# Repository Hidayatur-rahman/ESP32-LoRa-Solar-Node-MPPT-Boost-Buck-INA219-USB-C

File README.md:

# ESP32 LoRa Solar Node Meshtastic Board

A solar-powered ESP32 + LoRa (RFM95W) node board. It charges a single-cell Li-ion battery from a solar panel with MPPT (CN3791), generates stable 5V and 3.3V rails, monitors battery voltage and current (INA219), and programs over USB-C (CH340C with auto-reset).

**Board:** 2-layer PCB, 75 × 70 mm, 1.6 mm  
**Design tool:** KiCad 10  
**Revision:**  rev 1, 2026-10-13

## Table of Contents

- [3D View](#3d-view)
- [PCB](#pcb)
- [Features](#features)
- [Power Path](#power-path)
- [Pin Mapping](#pin-mapping)
- [Connectors](#connectors)
- [Solder Jumpers](#solder-jumpers)
- [MPPT Voltage Setting (CN3791)](#mppt-voltage-setting-cn3791)
- [MPPT Test Result](#mppt-test-result-bench-power-supply)
- [Main Components](#main-components)
- [Usage Notes](#usage-notes)
- [Firmware](#firmware)
- [Roadmap](#roadmap)
- [License](#license)
- [Disclaimer](#disclaimer)

## 3d View

## PCB

## Features

- ESP32-WROOM-32 module
- LoRa radio: RFM95W-915S2 (915 MHz) with U.FL antenna connector
- Solar MPPT charger: CN3791 for a 1S Li-ion/LiPo battery (4.2 V)
- Solder jumpers to set the solar panel MPPT voltage: 5 V / 9 V / 12 V / 18 V
- P-MOSFET (AOD4185) in the solar charge path
- INA219 current/voltage monitor with a 10 mΩ shunt on the battery line
- MT3608 boost converter (battery → 5 V)
- STI3408B buck converter (5 V → 3.3 V)
- USB-C programming port with CH340C and automatic reset/boot (DTR/RTS)
- Charge and done LEDs from the CN3791
- 2 × I2C ports and 3 × ADC sensor ports (JST-EH), each with selectable sensor supply (5 V or 3.3 V)
- Reset and Boot buttons
- Test points for 3.3 V, 5 V and 4.2 V
- 0 Ω links in the power path (useful for measuring current or isolating a section)

## Power Path

```
Solar panel ──► Q1 (P-MOSFET) ──► CN3791 MPPT ──► INA219 shunt ──► Battery (4.2 V)
                                                                       │
ESP32/LoRa / sensors ◄── 3.3 V(STI3408B buck) ◄── 5 V (MT3608 boost) ◄─┘
                                                              
```

> ⚠️ **BATTERY WARNING**  
> This board has **no BMS** and **no reverse polarity protection** on the battery input. The CN3791 only charges the cell, it does not protect it from over-discharge, over-current or short circuit. Connecting the battery the wrong way round can destroy the board and may cause a fire. **Always use a battery that already has a built-in BMS / protection circuit.**

## Pin Mapping

| ESP32 Pin | Function |
|---|---|
| GPIO18 | LoRa SCK |
| GPIO19 | LoRa MISO |
| GPIO23 | LoRa MOSI |
| GPIO4 | LoRa NSS (CS) |
| GPIO14 | LoRa RESET |
| GPIO26 | LoRa DIO0 |
| GPIO27 | LoRa DIO1 |
| GPIO21 | I2C SDA (INA219, J2, J3) |
| GPIO22 | I2C SCL (INA219, J2, J3) |
| GPIO32 | ADC port 1 (J7) |
| GPIO33 | ADC port 2 (J8) |
| GPIO34 | ADC port 3 (J9) |
| GPIO0 | Boot button / auto-reset |
| EN | Reset button / auto-reset |
| GPIO1 / GPIO3 | TX / RX to CH340C |

Each ADC input has a 10 kΩ / 15 kΩ divider, so a 5 V sensor output is scaled to about 3 V.

## Connectors

| Ref | Name | Description |
|---|---|---|
| J1 | USB-C | Programming and serial |
| J4 | U.FL | LoRa antenna |
| J5 | Battery | 1S Li-ion/LiPo (GND, BATT+) |
| J6 | Solar panel | Panel input (VCC, GND) |
| J2, J3 | I2C | SCL, SDA, 3.3 V, GND |
| J7, J8, J9 | ADC | Signal, sensor supply, GND |

## Solder Jumpers

| Ref | Function |
|---|---|
| 5V0, 9V1, 12V2, 18V3 | Select the solar panel MPPT voltage. Close only one. |
| JP1, JP3, JP4 | Select the supply of ADC port 1, 2 and 3: 5 V or 3.3 V |

he CN3791 regulates the solar panel voltage so that the MPPT pin sits at about 1.04 V (typical value from the datasheet; please verify against your datasheet revision). A resistor divider sets the panel voltage:
 
```
VCC (panel) ── R18 200k ──┬── MPPT pin
                          │
                        R_bottom (selected by jumper)
                          │
                         GND
 
V_panel = 1.04 V × (1 + R18 / R_bottom)
```
 
| Jumper | R_bottom | Regulated panel voltage | Suggested panel |
|---|---|---|---|
| 5V0 | R27 = 51 kΩ | ≈ 5.1 V | 5–6 V panel |
| 9V1 | R13 = 27 kΩ | ≈ 8.7 V | 9 V panel |
| 12V2 | R14 = 18 kΩ | ≈ 12.6 V | 12 V panel |
| 18V3 | R15 = 12 kΩ | ≈ 18.4 V | 20 V panel |
 
Use 1 % 0805 resistors. The values above are common values chosen to land close to the target panel voltage (within about 5 %), which is accurate enough because the maximum power point of a panel is fairly flat.
 
To use a different panel, choose the bottom resistor from the panel's maximum power voltage (Vmp):
 
```
R_bottom = R18 / (Vmp / 1.04 − 1)
```
 
Example: Vmp = 17 V → R_bottom = 200k / (17 / 1.04 − 1) ≈ 13 kΩ (use 13 kΩ or the nearest standard value, 12 kΩ or 15 kΩ).
 
Keep the panel's open-circuit voltage (Voc) below the CN3791 input limit (about 28 V).

## Mppt Test Result (Bench Power Supply)

The CN3791 charger was tested with a bench power supply instead of a solar panel, and the INA219 readings were compared with the supply readings.

| Item | Value |
|---|---|
| Input voltage (bench supply) | 18.6 V |
| Input current | 0.49 A |
| Input power | ≈ 9.1 W |
| INA219 bus voltage (battery) | 3.89 V |
| INA219 charge current | 2.04 A |
| Battery charge power | ≈ 7.9 W |
| Estimated efficiency | ≈ 87 % |

## Main Components

| Ref | Part |
|---|---|
| U1 | ESP32-WROOM-32 |
| U2 | RFM95W-915S2 (LoRa) |
| U3 | MT3608 (boost) |
| STI3408B1 | STI3408B (buck) |
| U4 | INA219 |
| U5 | CN3791 (MPPT charger) |
| U6 | CH340C (USB-UART) |
| Q1 | AOD4185 (P-MOSFET) |
| Q4, Q5 | BC847 (auto-reset) |
| RSHUNT1 | 0.01 Ω, 2512 |
| L1, L3 / L2 | 4.7 µH / 22 µH |

## Usage Notes

- Close **only one** MPPT jumper (5V0, 9V1, 12V2 or 18V3), based on your solar panel's maximum power voltage.
- Use a single-cell Li-ion/LiPo battery. The CN3791 in this design charges to 4.2 V.
- The RFM95W-915S2 covers the 915 MHz band. Check the allowed LoRa frequency in your country before use, and always attach an antenna before transmitting.
- Upload firmware over USB-C. Auto-reset is handled by the CH340C, so no button presses are needed.
- INA219 is on the I2C bus together with J2 and J3, so avoid address conflicts with your sensors.
- The INA219 address (0x40) is the default. Check the A0/A1 pins in the schematic if you changed it.

## Firmware

- Firmware: Meshtastic custom build
- Target: `esp32_rfm95_custom`
- Version: `2.8.3`
- Revision: `d9c9916`

| Signal | ESP32 Pin |
|---|---|
| SCK / MISO / MOSI | GPIO18 / GPIO19 / GPIO23 |
| NSS (CS) | GPIO4 |
| RESET | GPIO14 |
| DIO0 / DIO1 | GPIO26 / GPIO27 |
| I2C SDA / SCL | GPIO21 / GPIO22 |

Set the LoRa region in Meshtastic to match your country and the 915 MHz hardware.

## Roadmap
 
**Version 2 (in progress)**
<p align="center">
  
  \
</p>

- 4-layer PCB
- GPS module added

This repository currently contains version 1 (2-layer, no GPS). Version 2 files will be added when the design is ready.

## License

(KiCad schematic, PCB layout and design files): [CERN-OHL-W v2](https://ohwr.org/cern_ohl_w_v2.txt)

## Disclaimer

This is a hobbyist/DIY project. Double-check battery polarity and solar jumper settings before powering on. No warranty is provided — build and use at your own risk.

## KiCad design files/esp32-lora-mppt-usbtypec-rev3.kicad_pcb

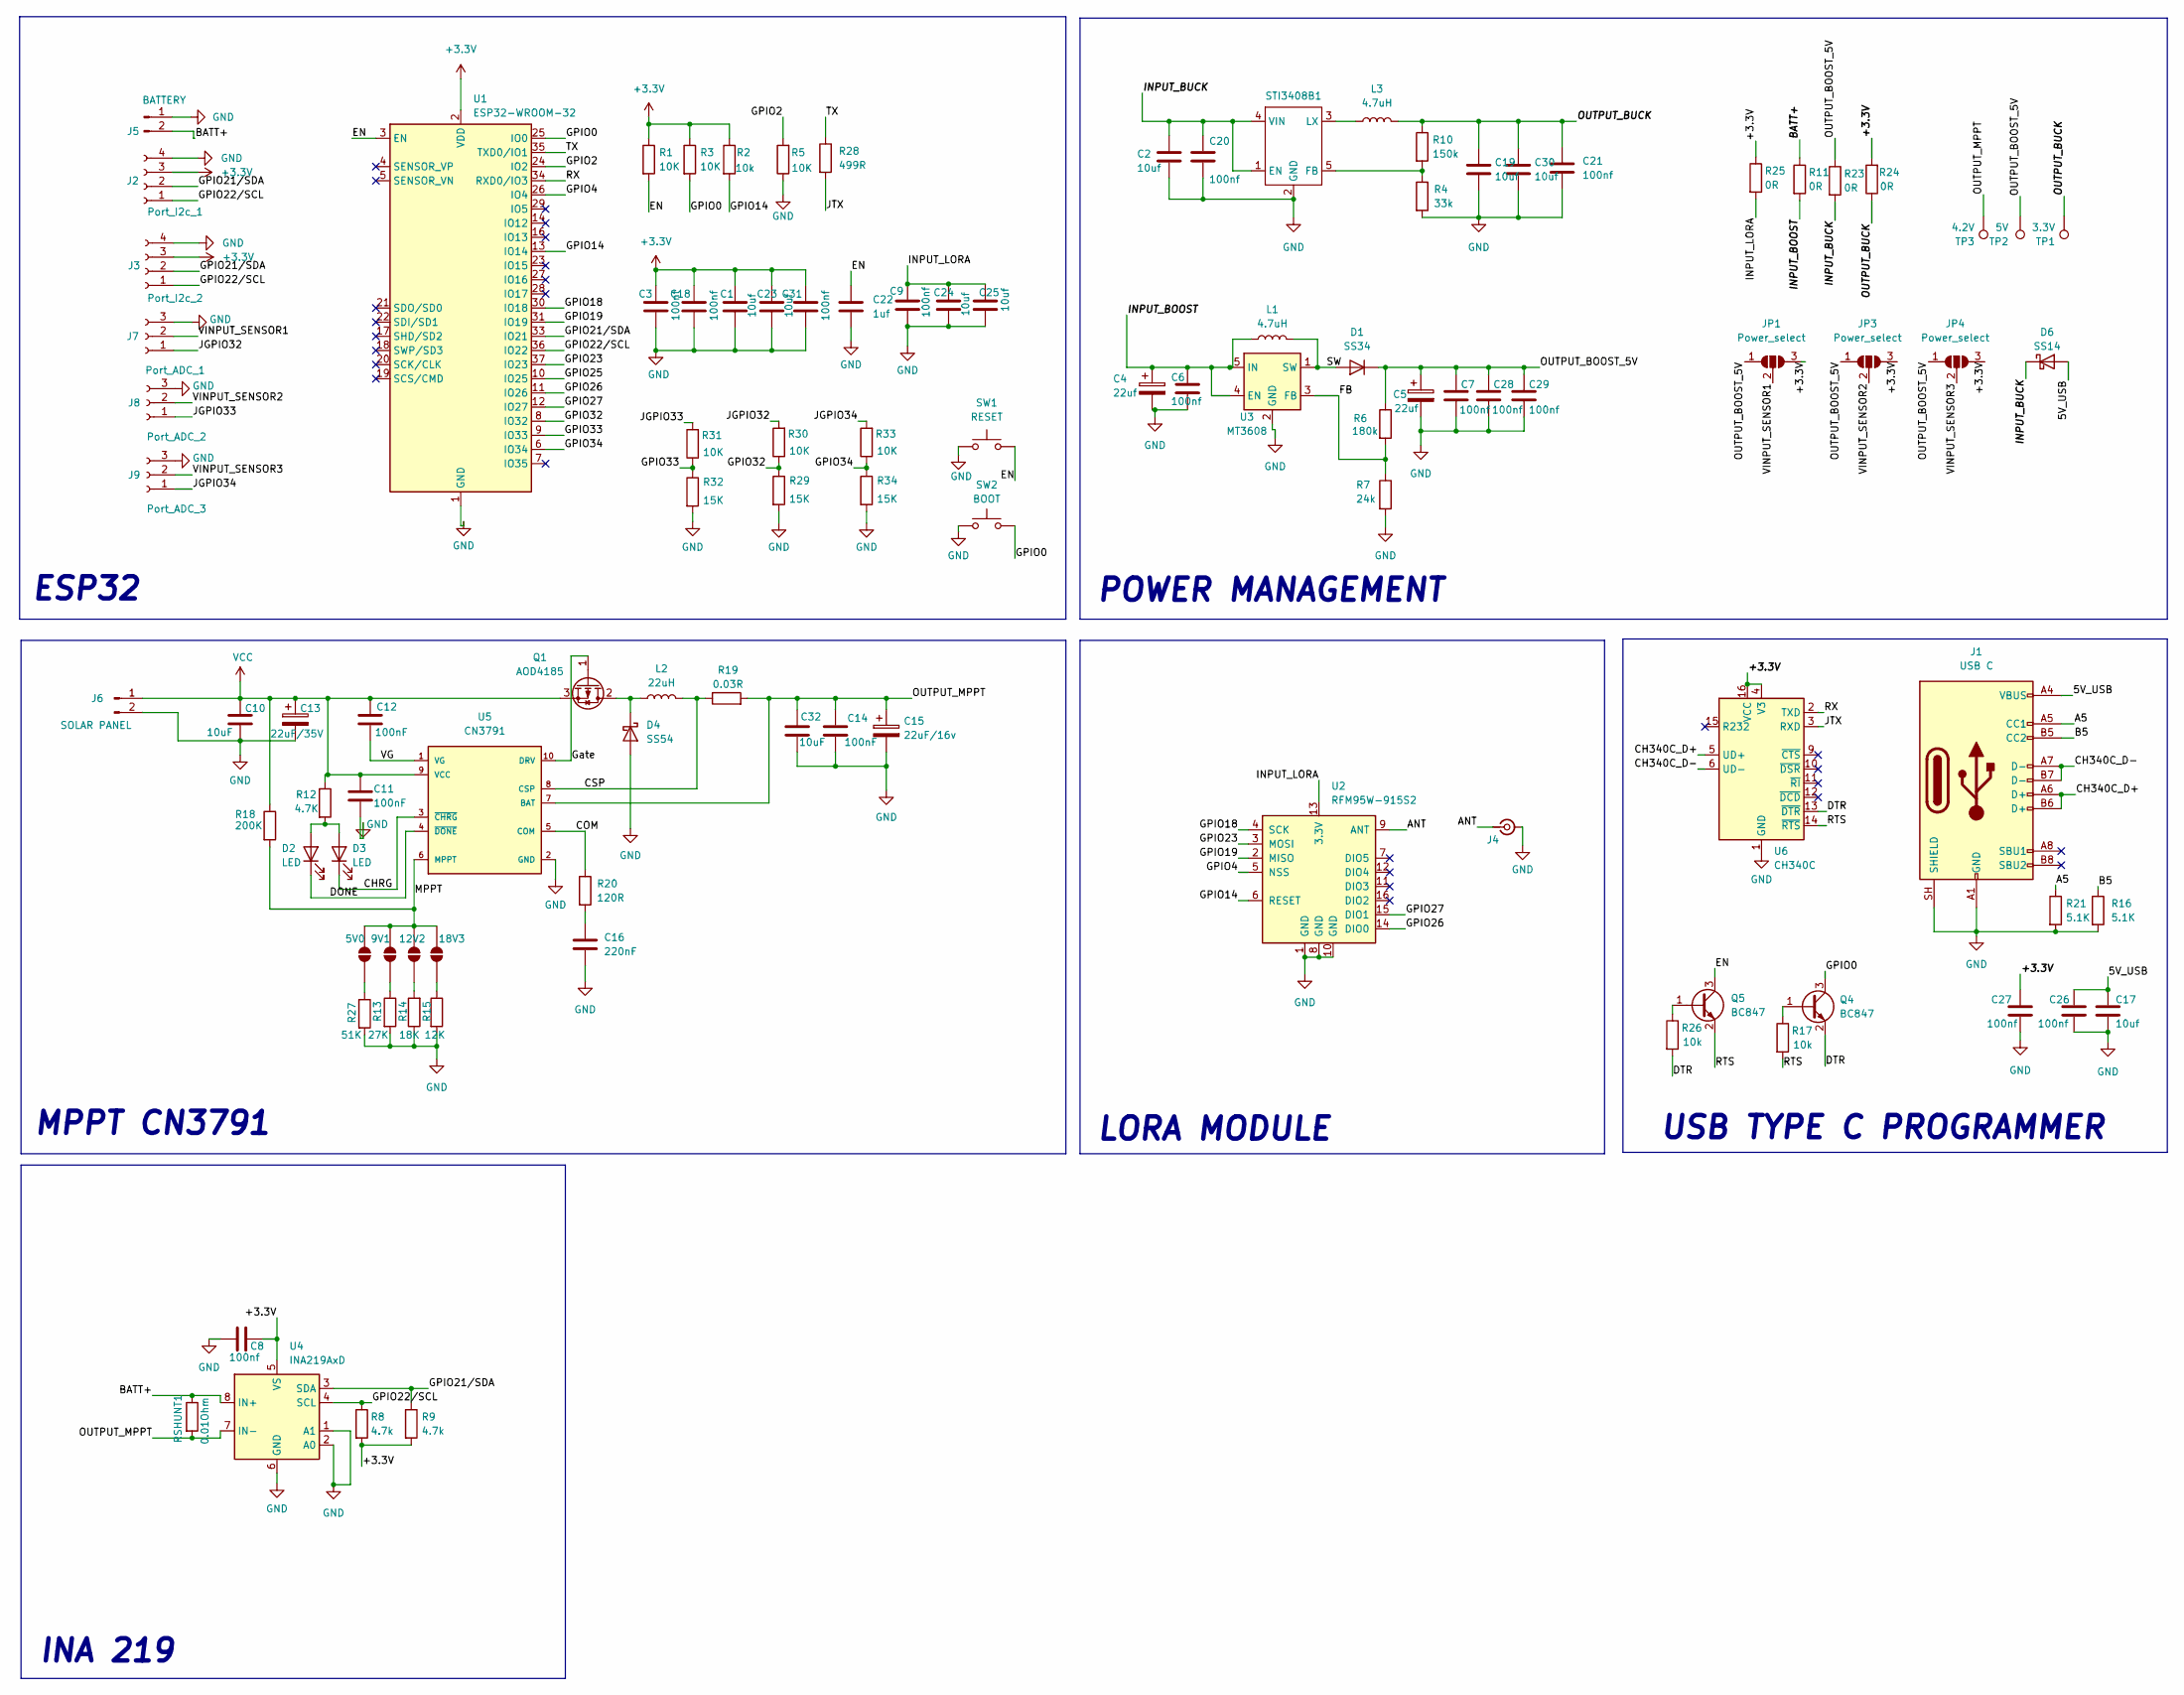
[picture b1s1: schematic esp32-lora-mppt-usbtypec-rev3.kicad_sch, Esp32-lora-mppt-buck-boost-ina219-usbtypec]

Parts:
5V0, 9V1, 12V2, 18V3: SolderJumper_2_Open; SolderJumper-2_P1.3mm_Open_RoundedPad1.0x1.5mm
C1, C2, C17, C19, C23, C24, C25, C30: 10uf; C_1206_3216Metric_Pad1.33x1.80mm_HandSolder
C3, C6, C7, C8, C9, C18, C20, C21, C26, C27, C28, C29, C31: 100nf; C_0603_1608Metric_Pad1.08x0.95mm_HandSolder
C4, C5: 22uf; C_1206_3216Metric_Pad1.33x1.80mm_HandSolder
C10, C32: 10uF; C_1206_3216Metric
C11, C12, C14: 100nF; C_0603_1608Metric_Pad1.08x0.95mm_HandSolder
C13: 22uF/35V; CP_Elec_8x6.9
C15: 22uF/16v; CP_Elec_8x6.9
C16: 220nF; C_0603_1608Metric_Pad1.08x0.95mm_HandSolder
C22: 1uf; C_0805_2012Metric_Pad1.18x1.45mm_HandSolder
D1: SS34; D_SMA
D2, D3: LED; LED_0805_2012Metric_Pad1.15x1.40mm_HandSolder
D4: SS54; D_SMA
D6: SS14; D_1206_3216Metric_Pad1.42x1.75mm_HandSolder
J1: USB C; USB_C_Receptacle_HCTL_HC-TYPE-C-16P-01A
J2: Port_I2c_1; JST_EH_B4B-EH-A_1x04_P2.50mm_Vertical
J3: Port_I2c_2; JST_EH_B4B-EH-A_1x04_P2.50mm_Vertical
J4: Conn_Coaxial_Small; U.FL_Molex_MCRF_73412-0110_Vertical
J5: BATTERY; JST_EH_B2B-EH-A_1x02_P2.50mm_Vertical
J6: SOLAR PANEL; JST_EH_B2B-EH-A_1x02_P2.50mm_Vertical
J7: Port_ADC_1; JST_EH_B3B-EH-A_1x03_P2.50mm_Vertical
J8: Port_ADC_2; JST_EH_B3B-EH-A_1x03_P2.50mm_Vertical
J9: Port_ADC_3; JST_EH_B3B-EH-A_1x03_P2.50mm_Vertical
JP1, JP3, JP4: Power_select; SolderJumper-3_P1.3mm_Open_RoundedPad1.0x1.5mm
L1, L3: 4.7uH; L_Changjiang_FXL0640
L2: 22uH; L_Changjiang_FXL1040
Q1: AOD4185; TO-252-2
Q4, Q5: BC847; SOT-23
R1, R3, R5: 10K; R_0805_2012Metric_Pad1.20x1.40mm_HandSolder
R2, R17, R26: 10k; R_0805_2012Metric_Pad1.20x1.40mm_HandSolder
R4: 33k; R_0805_2012Metric_Pad1.20x1.40mm_HandSolder
R6: 180k; R_0805_2012Metric_Pad1.20x1.40mm_HandSolder
R7: 24k; R_0805_2012Metric_Pad1.20x1.40mm_HandSolder
R8, R9: 4.7k; R_0805_2012Metric_Pad1.20x1.40mm_HandSolder
R10: 150k; R_0805_2012Metric_Pad1.20x1.40mm_HandSolder
R11, R23, R24, R25: 0R; R_0805_2012Metric_Pad1.20x1.40mm_HandSolder
R12: 4.7K; R_0805_2012Metric_Pad1.20x1.40mm_HandSolder
R13: 27K; R_0805_2012Metric_Pad1.20x1.40mm_HandSolder
R14: 18K; R_0805_2012Metric_Pad1.20x1.40mm_HandSolder
R15: 12K; R_0805_2012Metric_Pad1.20x1.40mm_HandSolder
R16, R21: 5.1K; R_0805_2012Metric_Pad1.20x1.40mm_HandSolder
R18: 200K; R_0805_2012Metric_Pad1.20x1.40mm_HandSolder
R19: 0.03R; R_2512_6332Metric_Pad1.40x3.35mm_HandSolder
R20: 120R; R_0805_2012Metric_Pad1.20x1.40mm_HandSolder
R27: 51K; R_0805_2012Metric_Pad1.20x1.40mm_HandSolder
R28: 499R; R_0805_2012Metric_Pad1.20x1.40mm_HandSolder
R29, R32, R34: 15K; R_0805_2012Metric
R30, R31, R33: 10K; R_0805_2012Metric
RSHUNT1: 0.01Ohm; R_2512_6332Metric_Pad1.40x3.35mm_HandSolder
STI3408B1: SOT-23-5
SW1: RESET; SW_SPST_TS-1088-xR020
SW2: BOOT; SW_SPST_TS-1088-xR020
TP1: 3.3V; TestPoint_Pad_1.0x1.0mm
TP2: 5V; TestPoint_Pad_1.0x1.0mm
TP3: 4.2V; TestPoint_Pad_1.0x1.0mm
U1: ESP32-WROOM-32
U2: RFM95W-915S2; HOPERF_RFM9XW_SMD
U3: MT3608; SOT-23-6
U4: INA219AxD; SOIC-8_3.9x4.9mm_P1.27mm
U5: CN3791; CN3791_SSOP10
U6: CH340C; SOIC-16_3.9x9.9mm_P1.27mm

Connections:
+3.3V: C1.1, C3.2, C8.2, C18.2, C23.1, C27.1, C31.2, J2.3, J3.3, JP1.3 (B), JP3.3 (B), JP4.3 (B), R1.1, R2.1, R3.1, R8.2, R9.2, R24.2, R25.1, U1.2 (VDD), U4.5 (VS), U6.4 (V3), U6.16 (VCC)
/<NO NET>: C17.1, C26.1, D6.2 (A), J1.A4 (VBUS), J1.A9 (VBUS), J1.B4 (VBUS), J1.B9 (VBUS)
/A5: J1.A5 (CC1), R21.1
/ANT: J4.1 (In), U2.9 (ANT)
/B5: J1.B5 (CC2), R16.1
/BATT+: J5.2, R11.1, RSHUNT1.1, U4.8 (IN+)
/CH340C_D+: J1.A6 (D+), J1.B6 (D+), U6.5 (UD+)
/CH340C_D-: J1.A7 (D-), J1.B7 (D-), U6.6 (UD-)
/CHRG: D3.1 (K), U5.3 (~CHRG)
/COM: R20.1, U5.5 (COM)
/CSP: L2.2, R19.1, U5.8 (CSP)
/DONE: D2.1 (K), U5.4 (~DONE)
/DTR: Q4.2 (E), R26.2, U6.13 (~DTR)
/EN: C22.1, Q5.3 (C), R1.2, SW1.2, U1.3 (EN)
/FB: R6.2, R7.1, U3.3 (FB)
/GPIO0: Q4.3 (C), R3.2, SW2.2, U1.25 (IO0)
/GPIO2: R5.2, U1.24 (IO2)
/GPIO4: U1.26 (IO4), U2.5 (NSS)
/GPIO14: R2.2, U1.13 (IO14), U2.6 (RESET)
/GPIO18: U1.30 (IO18), U2.4 (SCK)
/GPIO19: U1.31 (IO19), U2.2 (MISO)
/GPIO21/SDA: J2.2, J3.2, R9.1, U1.33 (IO21), U4.3 (SDA)
/GPIO22/SCL: J2.1, J3.1, R8.1, U1.36 (IO22), U4.4 (SCL)
/GPIO23: U1.37 (IO23), U2.3 (MOSI)
/GPIO25: U1.10 (IO25)
/GPIO26: U1.11 (IO26), U2.14 (DIO0)
/GPIO27: U1.12 (IO27), U2.15 (DIO1)
/GPIO32: R29.1, R30.1, U1.8 (IO32)
/GPIO33: R31.1, R32.1, U1.9 (IO33)
/GPIO34: R33.1, R34.1, U1.6 (IO34)
/Gate: Q1.1 (G), U5.10 (DRV)
/INPUT_BOOST: C4.1, C6.1, L1.1, R11.2, U3.4 (EN), U3.5 (IN)
/INPUT_BUCK: C2.1, C20.1, D6.1 (K), R23.2, STI3408B1.1 (EN), STI3408B1.4 (VIN)
/INPUT_LORA: C9.1, C24.1, C25.1, R25.2, U2.13 (3.3V)
/JGPIO32: J7.1, R30.2
/JGPIO33: J8.1, R31.2
/JGPIO34: J9.1, R33.2
/JTX: R28.2, U6.3 (RXD)
/MPPT: 5V0.2 (B), 9V1.2 (B), 12V2.1 (A), 18V3.2 (B), R18.2, U5.6 (MPPT)
/OUTPUT_BOOST_5V: C5.1, C7.1, C28.1, C29.1, D1.1 (K), JP1.1 (A), JP3.1 (A), JP4.1 (A), R6.1, R23.1, TP2.1 (1_1)
/OUTPUT_BUCK: C19.1, C21.1, C30.1, L3.2, R10.1, R24.1, TP1.1 (1_1)
/OUTPUT_MPPT: C14.1, C15.1, C32.1, R19.2, RSHUNT1.2, TP3.1 (1_1), U4.7 (IN-), U5.7 (BAT)
/RTS: Q5.2 (E), R17.2, U6.14 (~RTS)
/RX: U1.34 (RXD0/IO3), U6.2 (TXD)
/SW: D1.2 (A), L1.2, U3.1 (SW)
/TX: R28.1, U1.35 (TXD0/IO1)
/VG: C12.2, U5.1 (VG)
/VINPUT_SENSOR1: J7.2, JP1.2 (C)
/VINPUT_SENSOR2: J8.2, JP3.2 (C)
/VINPUT_SENSOR3: J9.2, JP4.2 (C)
GND: C1.2, C2.2, C3.1, C4.2, C5.2, C6.2, C7.2, C8.1, C9.2, C10.2, C11.2, C13.2, C14.2, C15.2, C16.2, C17.2, C18.1, C19.2, C20.2, C21.2, C22.2, C23.2, C24.2, C25.2, C26.2, C27.2, C28.2, C29.2, C30.2, C31.1, C32.2, D4.2 (A), J1.A1 (GND), J1.A12 (GND), J1.B1 (GND), J1.B12 (GND), J1.SH (SHIELD), J2.4, J3.4, J4.2 (Ext), J5.1, J6.2, J7.3, J8.3, J9.3, R4.2, R5.1, R7.2, R13.2, R14.1, R15.2, R16.2, R21.2, R27.2, R29.2, R32.2, R34.2, STI3408B1.2 (GND), SW1.1, SW2.1, U1.1 (GND), U1.15 (GND), U1.38 (GND), U1.39 (GND), U2.1 (GND), U2.8 (GND), U2.10 (GND), U3.2 (GND), U4.1 (A1), U4.2 (A0), U4.6 (GND), U5.2 (GND), U6.1 (GND)
unnamed: 5V0.1 (A), R27.1
unnamed: 9V1.1 (A), R13.1
unnamed: 12V2.2 (B), R14.2
unnamed: 18V3.1 (A), R15.1
unnamed: C16.1, R20.2
unnamed: D2.2 (A), D3.2 (A), R12.2
unnamed: D4.1 (K), L2.1, Q1.2 (D)
unnamed: Q4.1 (B), R17.1
unnamed: Q5.1 (B), R26.1
unnamed: R4.1, R10.2, STI3408B1.5 (FB)
unnamed: L3.1, STI3408B1.3 (LX)
VCC: C10.1, C11.1, C12.1, C13.1, J6.1, Q1.3 (S), R12.1, R18.1, U5.9 (VCC)

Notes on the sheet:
MPPT CN3791
INA 219
ESP32
USB TYPE C PROGRAMMER
POWER MANAGEMENT
LORA MODULE

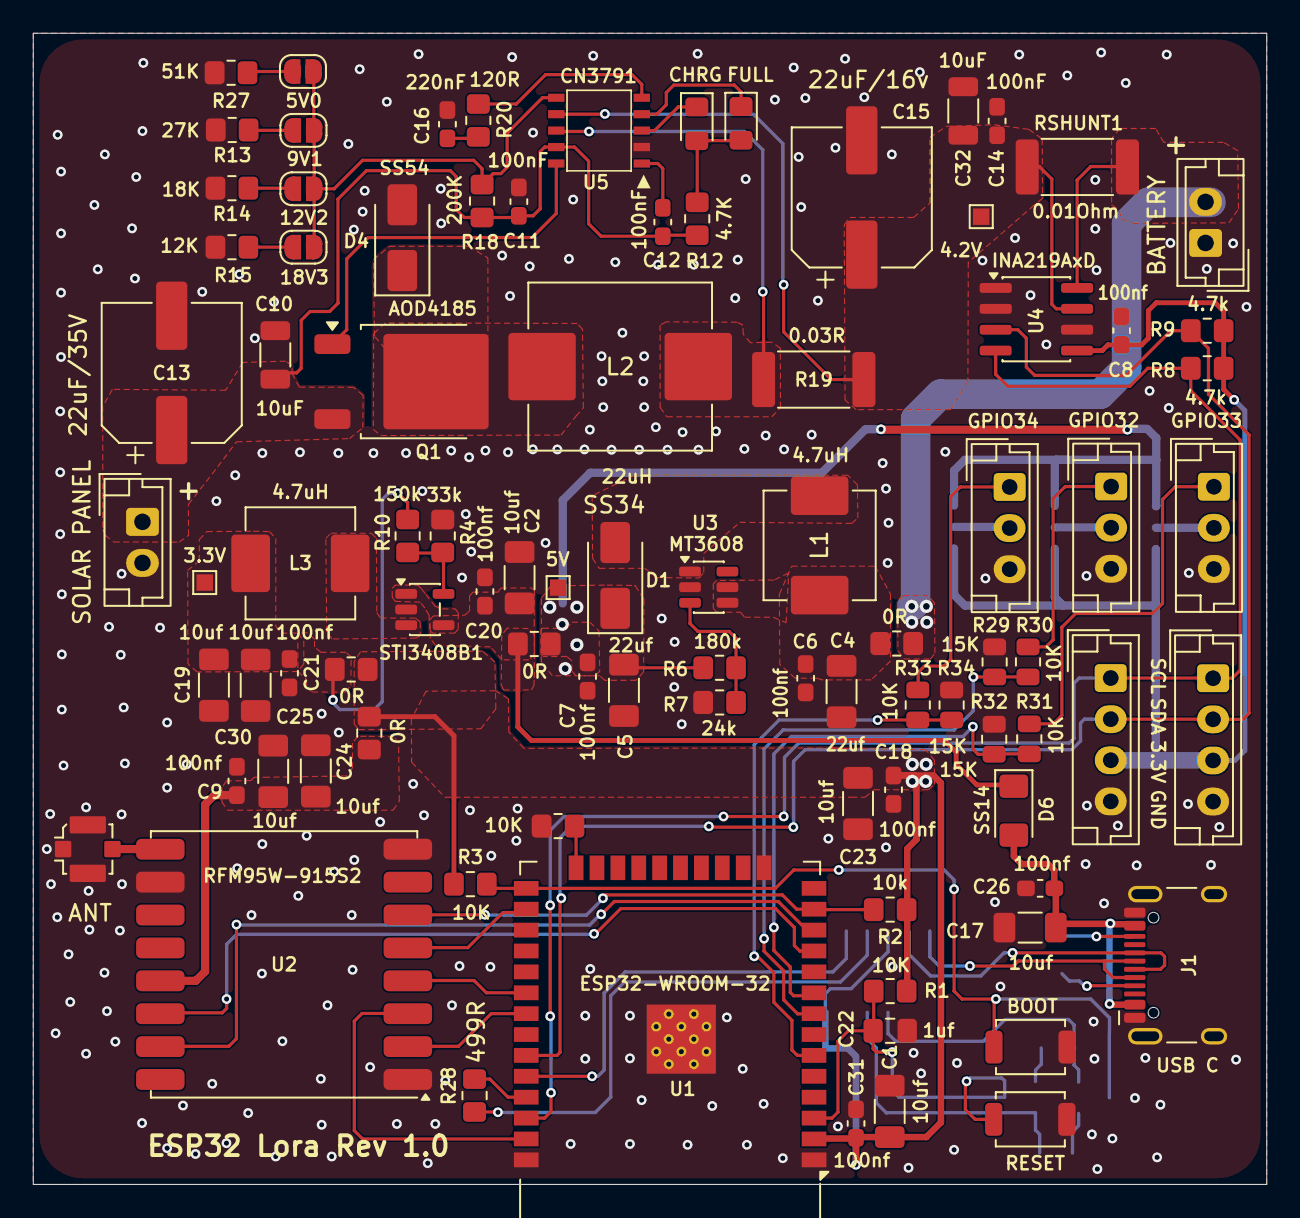
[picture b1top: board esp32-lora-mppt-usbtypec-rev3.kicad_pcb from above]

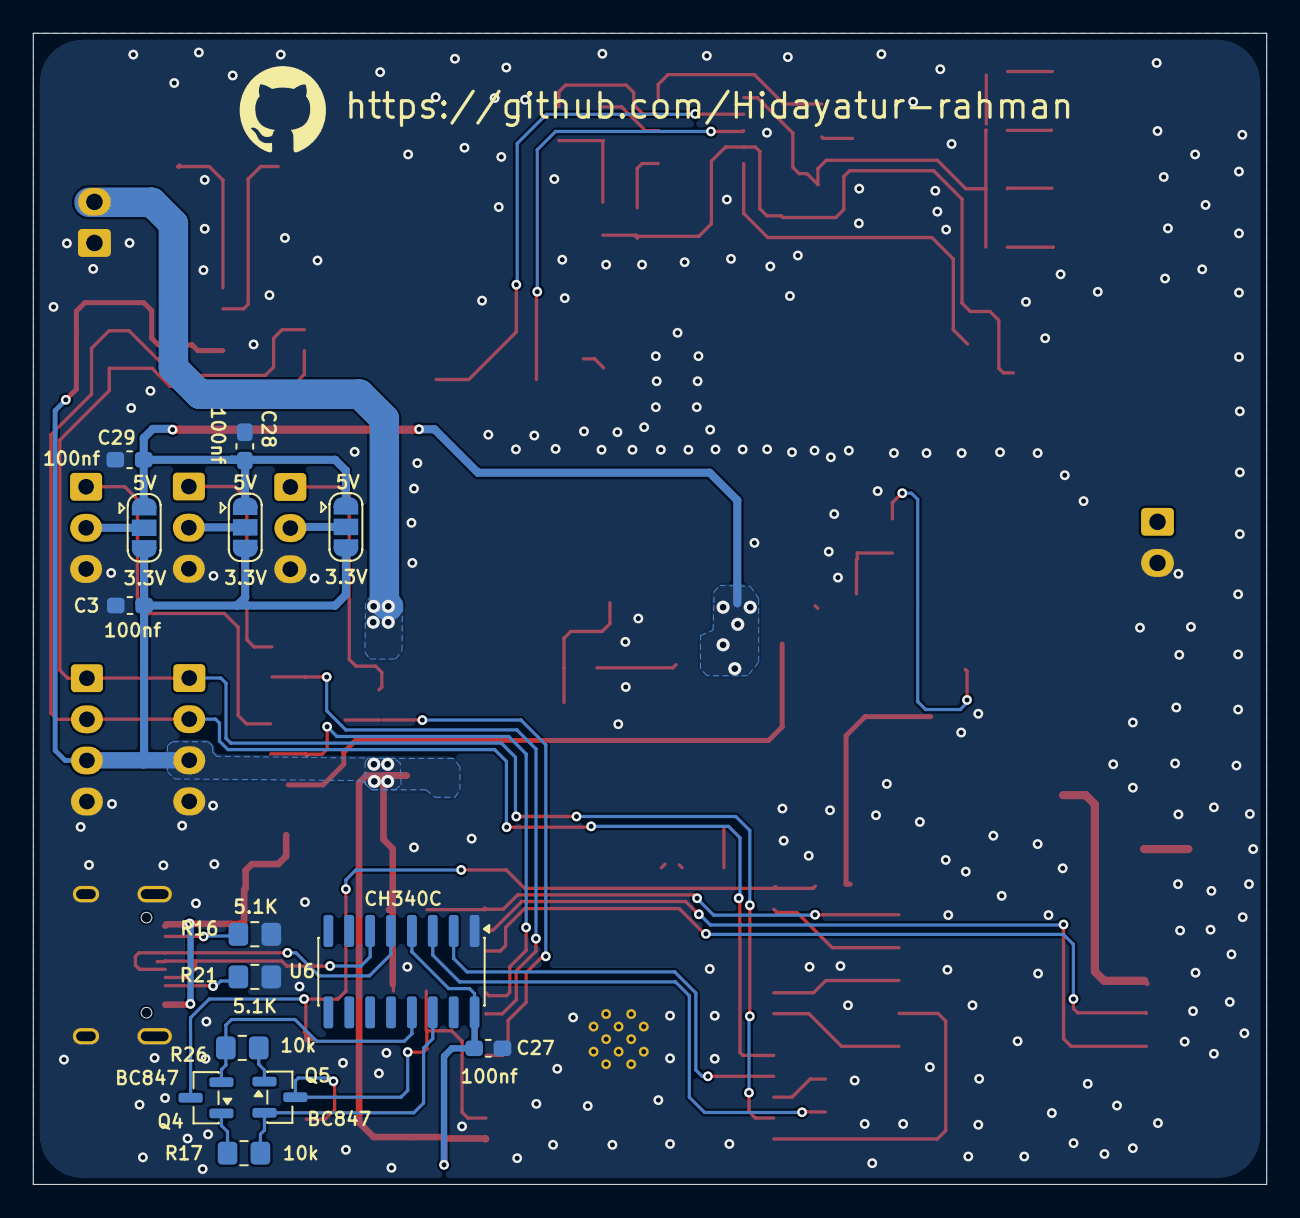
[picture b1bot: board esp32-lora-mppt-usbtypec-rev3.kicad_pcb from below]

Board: 2 copper layers, 75.0 x 70.0 mm, 105 parts (14 on the bottom side), 62 nets.
